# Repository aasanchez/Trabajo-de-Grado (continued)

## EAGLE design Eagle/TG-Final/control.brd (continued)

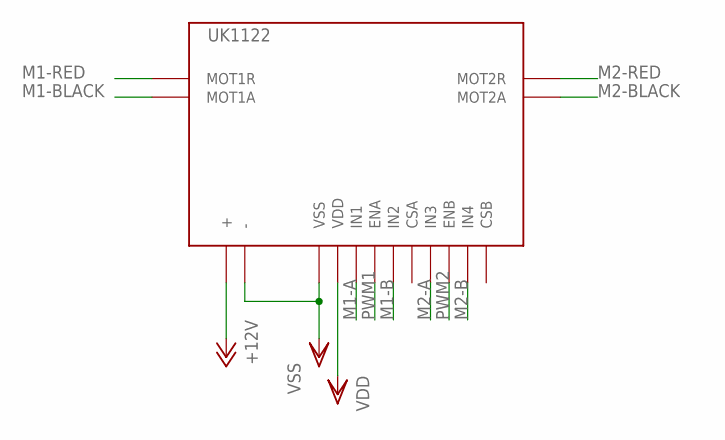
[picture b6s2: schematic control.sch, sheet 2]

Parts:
UK1122: UK1122

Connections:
+12V: UK1122.+; also elsewhere on the board
M1-A: UK1122.IN1; also elsewhere on the board
M1-B: UK1122.EN2 (IN2); also elsewhere on the board
M1-BLACK: UK1122.MOT1A; also elsewhere on the board
M1-RED: UK1122.MOT1R; also elsewhere on the board
M2-A: UK1122.IN3; also elsewhere on the board
M2-B: UK1122.IN4; also elsewhere on the board
M2-BLACK: UK1122.MOT2A; also elsewhere on the board
M2-RED: UK1122.MOT2R; also elsewhere on the board
PWM1: UK1122.ENA; also elsewhere on the board
PWM2: UK1122.ENB; also elsewhere on the board
VDD: UK1122.+5 (VDD); also elsewhere on the board
VSS: UK1122.-, UK1122.GND (VSS); also elsewhere on the board

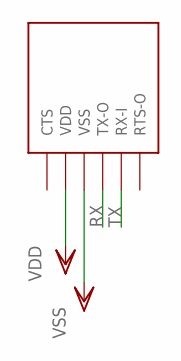
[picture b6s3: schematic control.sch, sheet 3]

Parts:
U$3: BLUESMIRF

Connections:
RX: U$3.TX-O; also elsewhere on the board
TX: U$3.RX-I; also elsewhere on the board
VDD: U$3.VDD; also elsewhere on the board
VSS: U$3.VSS; also elsewhere on the board

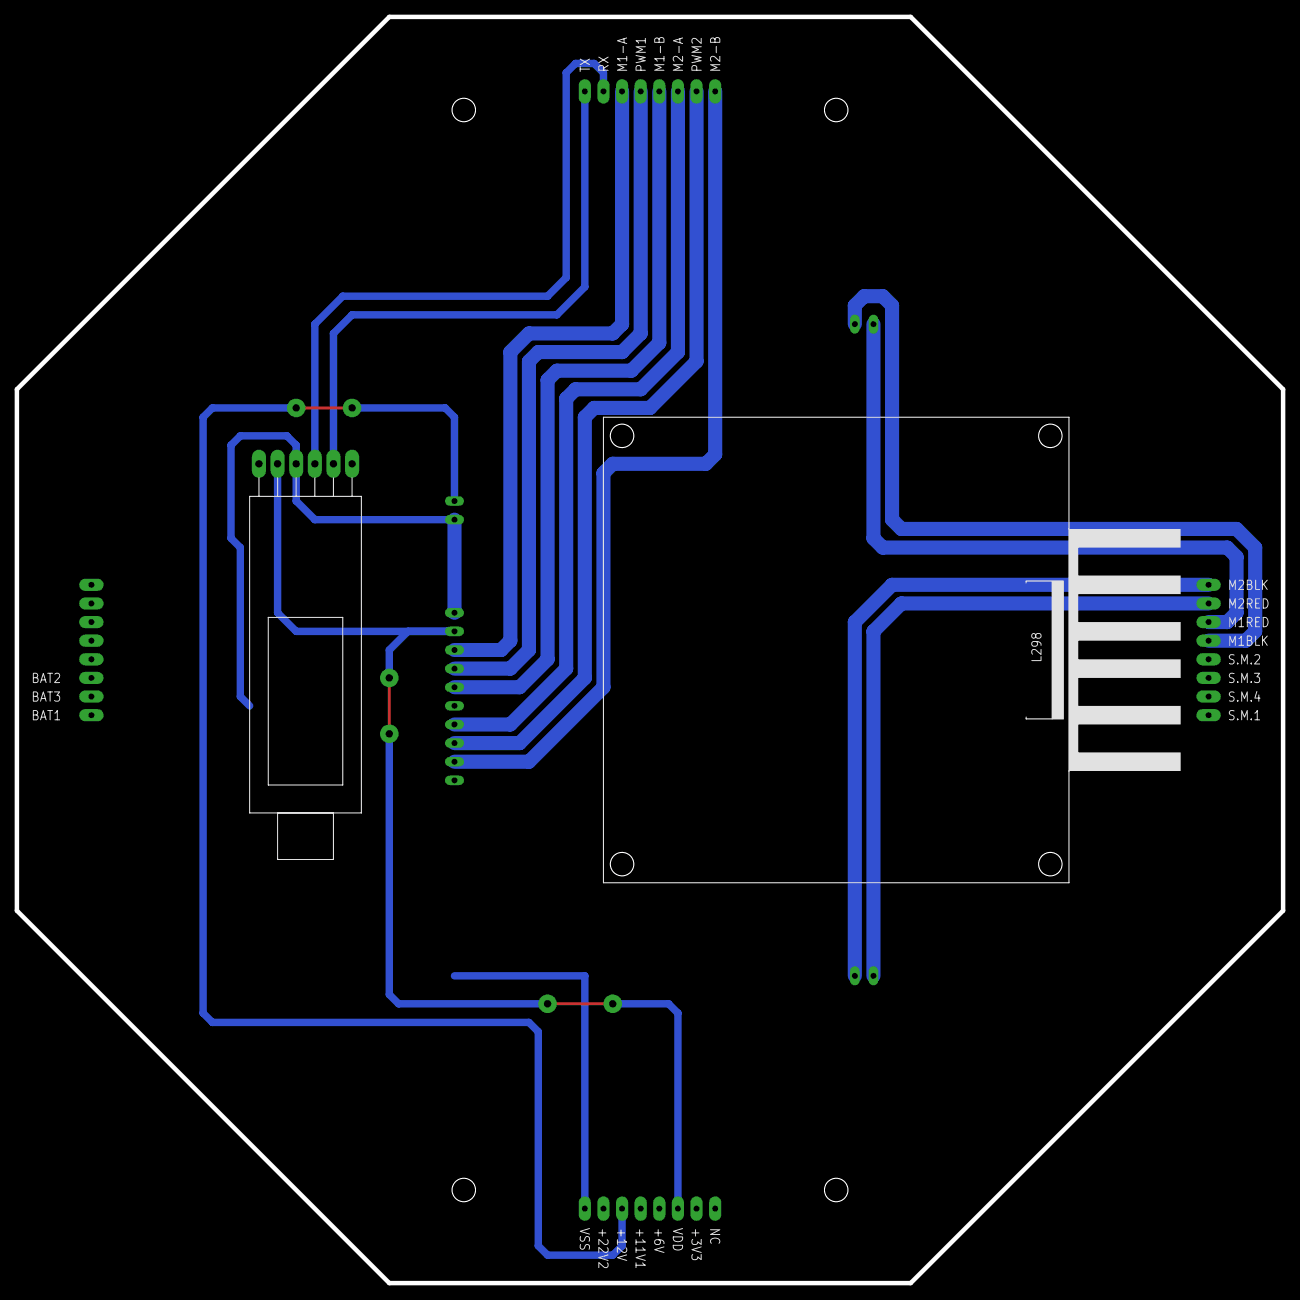
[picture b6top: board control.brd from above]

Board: 2 copper layers, 172.7 x 172.7 mm, 3 parts (0 on the bottom side), 15 nets.

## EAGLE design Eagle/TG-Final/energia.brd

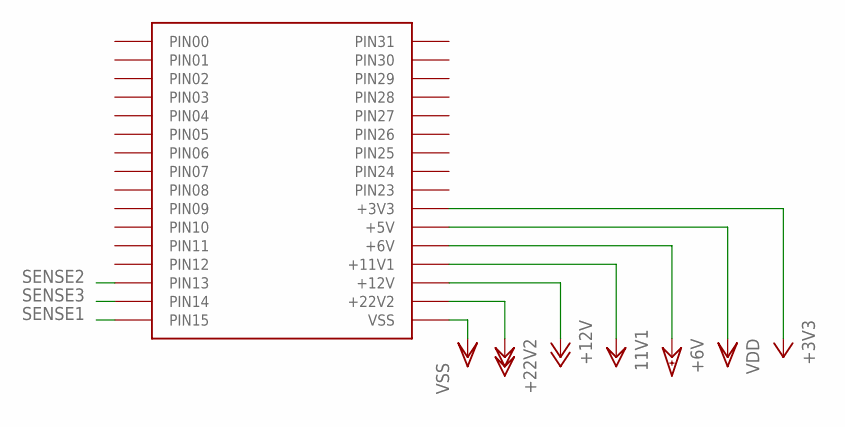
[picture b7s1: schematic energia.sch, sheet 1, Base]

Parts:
U$1: BASE

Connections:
+3V3: U$1.PIN22 (+3V3); also elsewhere on the board
+6V: U$1.PIN20 (+6V); also elsewhere on the board
+11V1: U$1.PIN19 (+11V1); also elsewhere on the board
+12V: U$1.PIN18 (+12V); also elsewhere on the board
+22V: U$1.PIN17 (+22V2); also elsewhere on the board
SENSE1: U$1.PIN15; also elsewhere on the board
SENSE2: U$1.PIN13; also elsewhere on the board
SENSE3: U$1.PIN14; also elsewhere on the board
VDD: U$1.PIN21 (+5V); also elsewhere on the board
VSS: U$1.PIN16 (VSS); also elsewhere on the board

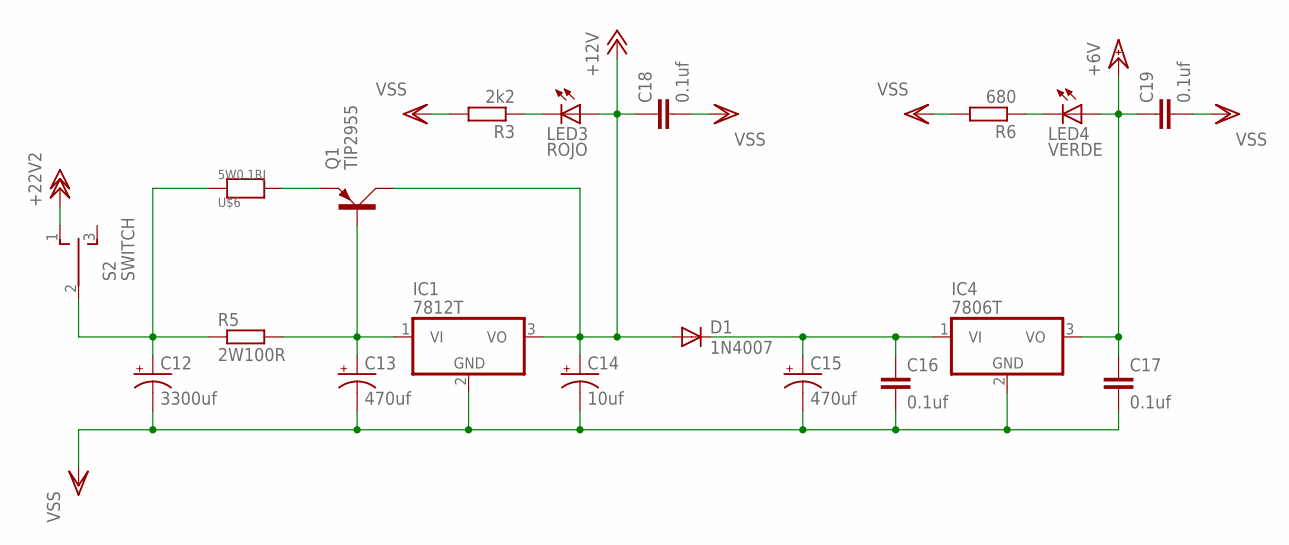
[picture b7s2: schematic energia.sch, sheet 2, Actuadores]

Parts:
C12: 3300uf; E7,5-18
C13, C15: 470uf; E3,5-8
C14: 10uf; E2,5-5
C16, C17, C18, C19: 0.1uf; C050-024X044
D1: 1N4007; DO41-10
IC1: 7812T; TO220H
IC4: 7806T; TO220H
LED3: ROJO; LED3MM
LED4: VERDE; LED3MM
Q1: TIP2955; TOP3AV
R3: 2k2; 0204/5
R5: 2W100R; 0411/12
R6: 680; 0204/5
S2: SWITCH; TL3XYO
U$6: 5W0.1RJ; RES-22X10

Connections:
+6V: C17.1, C19.1, IC4.3 (VO), LED4.A; also elsewhere on the board
+12V: C14.+, C18.1, D1.A, IC1.3 (VO), LED3.A, Q1.C; also elsewhere on the board
+22V: S2.1 (O); also elsewhere on the board
unnamed: LED3.K (C), R3.1
unnamed: C12.+, R5.1, S2.2, U$6.P$1
unnamed: Q1.E, U$6.P$2
unnamed: C13.+, IC1.1 (VI), Q1.B, R5.2
unnamed: LED4.K (C), R6.1
unnamed: C15.+, C16.1, D1.C, IC4.1 (VI)
VSS: C12.-, C13.-, C14.-, C15.-, C16.2, C17.2, C18.2, C19.2, IC1.2 (GND), IC4.2 (GND), R3.2, R6.2; also elsewhere on the board

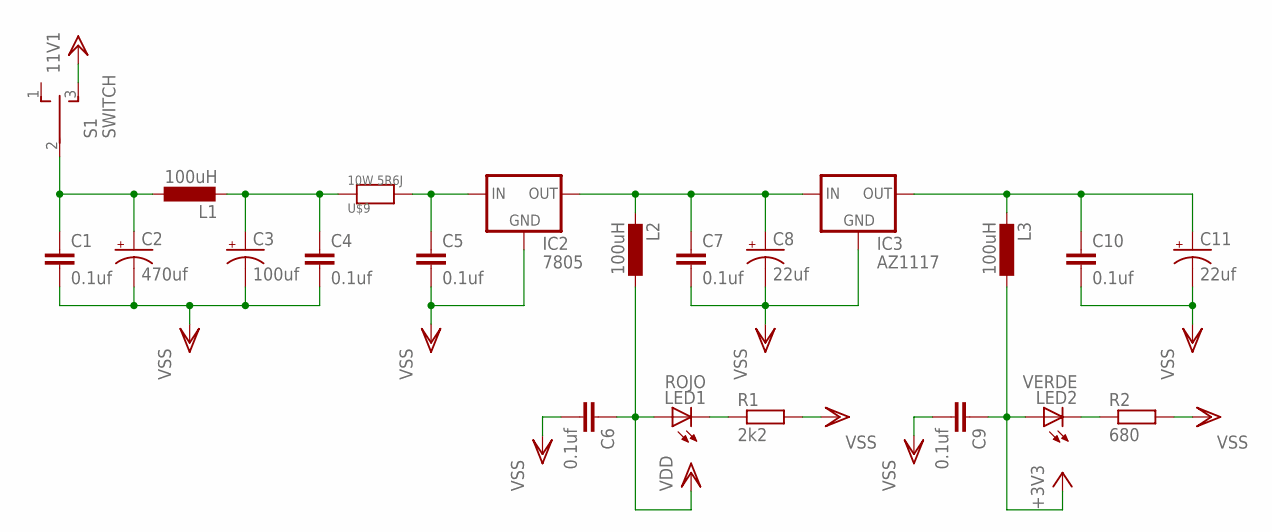
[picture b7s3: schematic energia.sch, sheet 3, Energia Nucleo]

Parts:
C1, C4, C5, C6, C7, C9, C10: 0.1uf; C050-024X044
C2: 470uf; E2,5-7
C3: 100uf; E2,5-7
C8, C11: 22uf; E2,5-7
IC2: 7805; TO-220-ALT
IC3: AZ1117; 78XXL
L1: 100uH; TFI0307
L2, L3: 100uH; 0207/7
LED1: ROJO; LED3MM
LED2: VERDE; LED3MM
R1: 2k2; 0204/5
R2: 680; 0204/5
S1: SWITCH; TL3XYO
U$9: 10W 5R6J; RES-49X10

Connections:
+3V3: C9.1, L3.1, LED2.A; also elsewhere on the board
+11V1: S1.3 (S); also elsewhere on the board
unnamed: C1.1, C2.+, L1.1, S1.2
unnamed: C5.1, IC2.IN, U$9.P$2
unnamed: C3.+, C4.1, L1.2, U$9.P$1
unnamed: C7.1, C8.+, IC2.OUT, IC3.OUT (IN), L2.2
unnamed: LED1.K (C), R1.1
unnamed: C10.1, C11.+, IC3.GND (OUT), L3.2
unnamed: LED2.K (C), R2.1
VDD: C6.1, L2.1, LED1.A; also elsewhere on the board
VSS: C1.2, C2.-, C3.-, C4.2, C5.2, C6.2, C7.2, C8.-, C9.2, C10.2, C11.-, IC2.GND, IC3.IN (GND), R1.2, R2.2; also elsewhere on the board

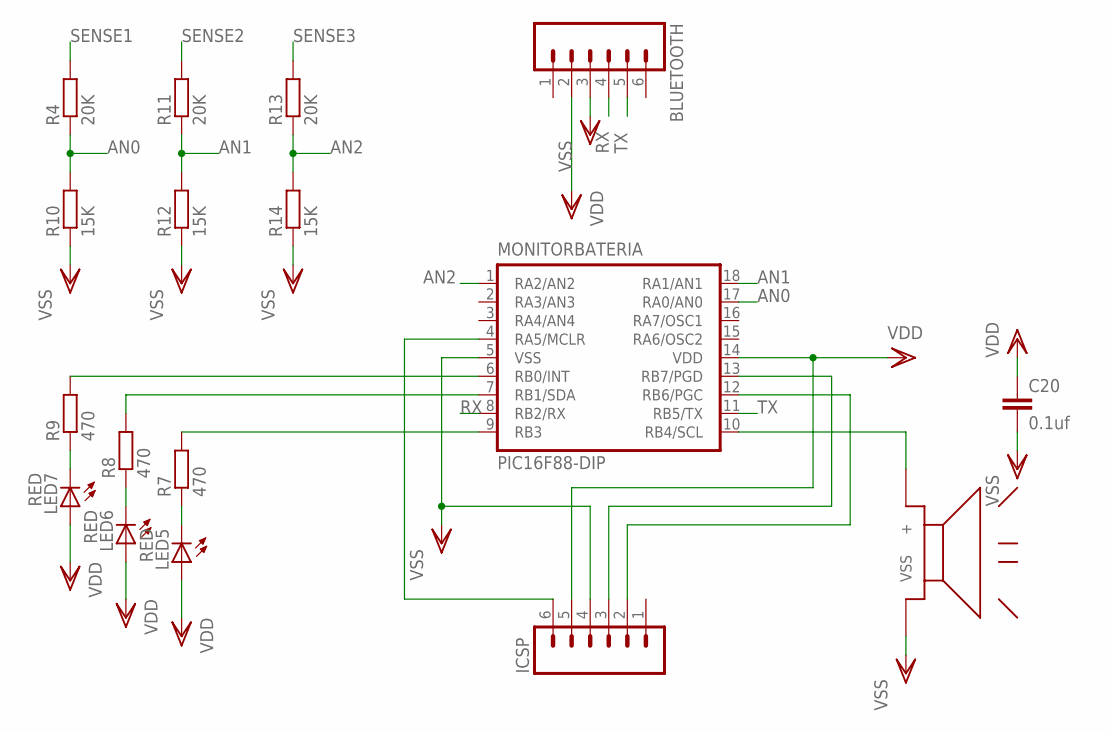
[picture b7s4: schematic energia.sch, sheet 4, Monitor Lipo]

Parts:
BLUETOOTH: 1X06_LONGPADS
C20: 0.1uf; C050-024X044
ICSP: 1X06_LONGPADS
LED5, LED6, LED7: RED; LED3MM
MONITORBATERIA: PIC16F88-DIP; DIL18
R4, R11, R13: 20K; 0204/5
R7, R8, R9: 470; 0204/5
R10, R12, R14: 15K; 0204/5
U$10: BUZZER

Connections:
AN0: MONITORBATERIA.17 (RA0/AN0), R4.1, R10.2
AN1: MONITORBATERIA.18 (RA1/AN1), R11.1, R12.2
AN2: MONITORBATERIA.1 (RA2/AN2), R13.1, R14.2
unnamed: ICSP.6, MONITORBATERIA.4 (RA5/MCLR)
unnamed: ICSP.3, MONITORBATERIA.13 (RB7/PGD)
unnamed: ICSP.2, MONITORBATERIA.12 (RB6/PGC)
unnamed: LED5.K (C), R7.1
unnamed: LED7.K (C), R9.1
unnamed: LED6.K (C), R8.1
unnamed: MONITORBATERIA.6 (RB0/INT), R9.2
unnamed: MONITORBATERIA.7 (RB1/SDA), R8.2
unnamed: MONITORBATERIA.9 (RB3), R7.2
unnamed: MONITORBATERIA.10 (RB4/SCL), U$10.+
RX: BLUETOOTH.4, MONITORBATERIA.8 (RB2/RX)
SENSE1: R4.2; also elsewhere on the board
SENSE2: R11.2; also elsewhere on the board
SENSE3: R13.2; also elsewhere on the board
TX: BLUETOOTH.5, MONITORBATERIA.11 (RB5/TX)
VDD: BLUETOOTH.2, C20.1, ICSP.5, LED5.A, LED6.A, LED7.A, MONITORBATERIA.14 (VDD); also elsewhere on the board
VSS: BLUETOOTH.3, C20.2, ICSP.4, MONITORBATERIA.5 (VSS), R10.1, R12.1, R14.1, U$10.- (VSS); also elsewhere on the board

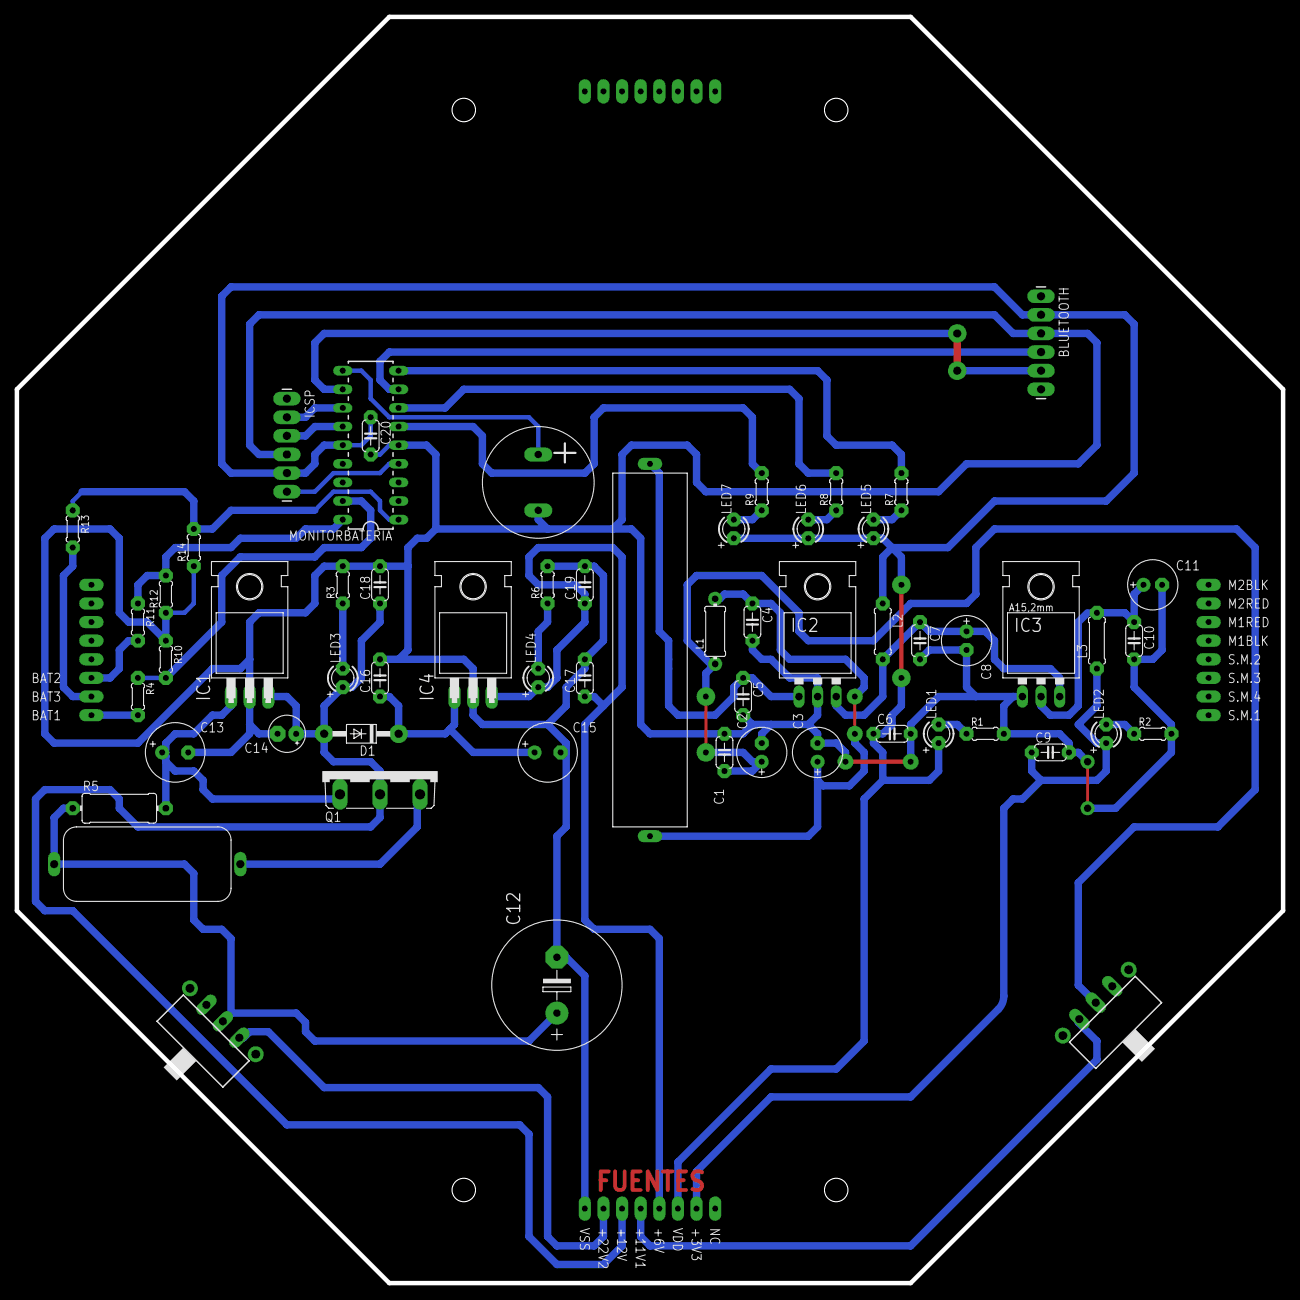
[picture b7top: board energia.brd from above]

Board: 2 copper layers, 172.7 x 172.7 mm, 59 parts (0 on the bottom side), 38 nets.

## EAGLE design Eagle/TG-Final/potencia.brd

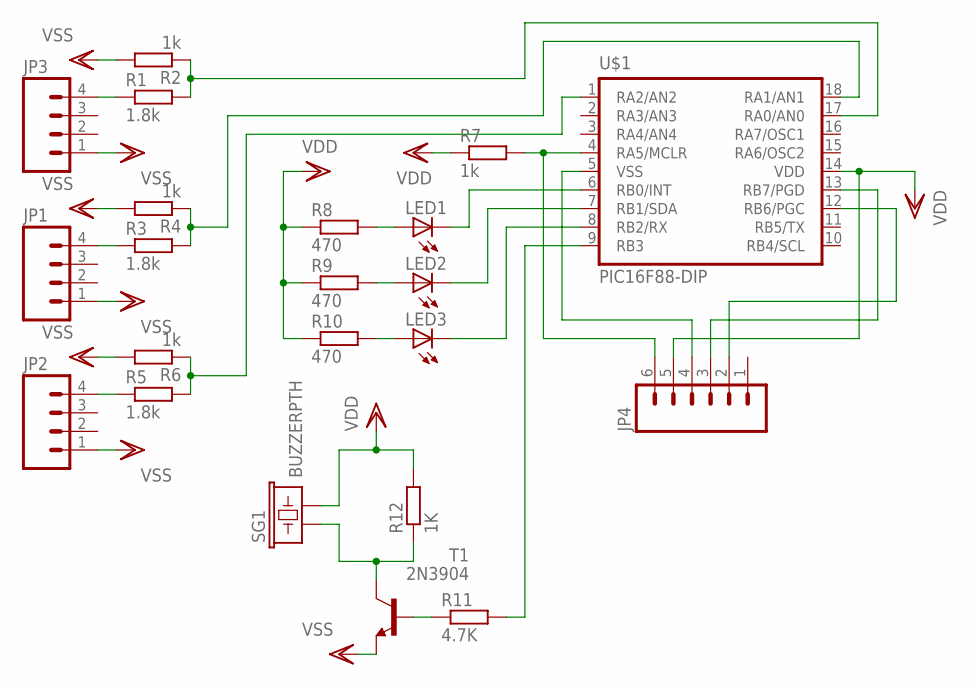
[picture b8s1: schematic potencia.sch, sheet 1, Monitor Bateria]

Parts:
JP1, JP2, JP3: M04LONGPADS; 1X04_LONGPADS
JP4: M06LONGPADS; 1X06_LONGPADS
LED1, LED2, LED3: LED3MM
R1, R3, R5: 1.8k; 0204/5
R2, R4, R6, R7: 1k; 0204/5
R8, R9, R10: 470; 0204/5
R11: 4.7K; 0204/5
R12: 1K; 0204/5
SG1: BUZZERPTH; BUZZER-12MM
T1: 2N3904; TO92
U$1: PIC16F88-DIP; DIL18

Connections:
unnamed: JP3.4, R1.1
unnamed: R1.2, R2.1, U$1.17 (RA0/AN0)
unnamed: JP1.4, R3.1
unnamed: R3.2, R4.1, U$1.18 (RA1/AN1)
unnamed: JP2.4, R5.1
unnamed: R5.2, R6.1, U$1.1 (RA2/AN2)
unnamed: JP4.4, U$1.5 (VSS)
unnamed: LED1.K (C), U$1.6 (RB0/INT)
unnamed: LED2.K (C), U$1.7 (RB1/SDA)
unnamed: LED3.K (C), U$1.8 (RB2/RX)
unnamed: LED1.A, R8.2
unnamed: JP4.3, U$1.13 (RB7/PGD)
unnamed: LED2.A, R9.2
unnamed: LED3.A, R10.2
unnamed: JP4.2, U$1.12 (RB6/PGC)
unnamed: JP4.6, R7.2, U$1.4 (RA5/MCLR)
unnamed: R11.2, U$1.9 (RB3)
unnamed: R11.1, T1.2 (B)
unnamed: R12.1, SG1.+ (1), T1.1 (C)
VDD: JP4.5, R7.1, R8.1, R9.1, R10.1, R12.2, SG1.- (2), U$1.14 (VDD)
VSS: JP1.1, JP2.1, JP3.1, R2.2, R4.2, R6.2, T1.3 (E); also elsewhere on the board

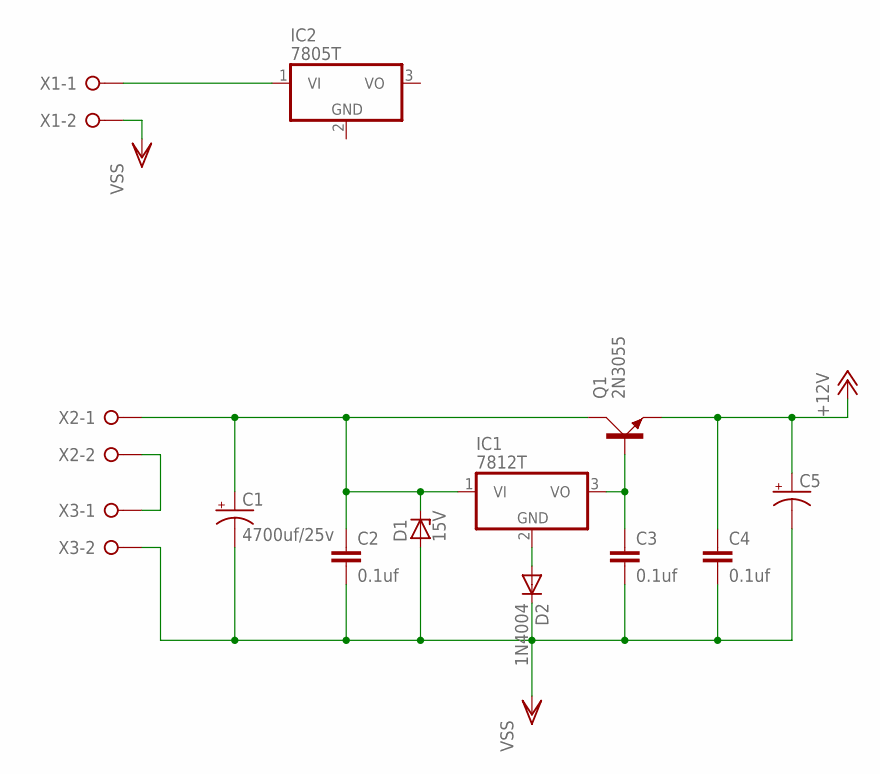
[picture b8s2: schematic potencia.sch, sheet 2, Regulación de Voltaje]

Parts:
C1: 4700uf/25v; EB30D
C2, C3, C4: 0.1uf; C050-024X044
C5: CPOL-USE2.5-6; E2,5-6
D1: 15V; F126Z10
D2: 1N4004; DO41-10
IC1: 7812T; TO220H
IC2: 7805T; TO220H
Q1: 2N3055; TO3A
X1, X2, X3: W237-2N

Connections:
+12V: C4.1, C5.+, Q1.E
unnamed: X2.2, X3.1
unnamed: C1.+, C2.1, D1.C, IC1.1 (VI), Q1.C, Q1.C1 (C), X2.1
unnamed: C3.1, IC1.3 (VO), Q1.B
unnamed: IC2.1 (VI), X1.1
unnamed: D2.A, IC1.2 (GND)
VSS: C1.-, C2.2, C3.2, C4.2, C5.-, D1.A, D2.C, X1.2, X3.2; also elsewhere on the board

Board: 2 copper layers, 35 parts (0 on the bottom side), 27 nets, no tracks yet.

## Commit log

2011-08-24 Primer commit
2011-10-05 codigo muñeco
2011-10-15 Actualizaciones General
2011-11-10 Lista de Compras
2012-01-18 Comienzo
2012-02-07 Actualizaciones Varias
2012-02-09 pySerial
2012-02-09 Limpiando
2012-02-13 Fixed
2012-02-13 Limpieza Profunda
2012-02-15 Codigo para graficas señales cortesia de Yeison Cardona
2012-02-16 Monitor Lipo
2012-02-16 Lectura 3 canales monitor de baterias
2012-02-16 Salidas en led alarma lipo
2012-02-16 Listo Codigo monitoreo Lipo 16f88
2012-02-16 inicio comunicacion CDC
2012-02-16 Graficas de IMU
2012-02-20 Inicio de Codigo Final
2012-02-20 Intento obtener datos del imu e una funcion
2012-02-22 Calibracion de Sensores
2012-02-22 Lectura y Optimizacion de Codigo
2012-02-23 Correccion para ADXL345 Eje Z, y graficas separadas
2012-02-24 Aceleración Angular
2012-03-01 Run Led
2012-03-02 Adquisición de sensores, limpieza de ruido y de calculo de zero, el cálculo del ángulo
2012-03-02 Filtro de Kalman
2012-03-02 iniciando de 298
2012-03-02 Fix Pin l298
2012-03-05 Comienzo de Control para Muñeco de Madera
2012-03-07 Diseño CAD y otros
2012-03-07 Schematic para Potencia
2012-03-08 Esquematicos de Alimentación
2012-03-08 Esquematicos para placa logica
2012-03-08 Fix Pins Motor 1, Avances en Esquematicos
2012-03-08 Limpieza, manual
2012-03-14 Placa de Actuadores y Otros
2012-03-14 Routing placa Actuadores
2012-03-14 Routing placa Actuadores. Listo??
2012-03-15 Mejoras en placa de Actuadores y otros
2012-03-16 Comienzo placa potencia
2012-03-19 Fuente 11.1v -> 5v y 3v3
2012-03-19 Monitor Baterias LiPO
2012-03-20 Correcciones varias
2012-03-23 Fuente de Potencia
2012-03-25 Trabajos en la Sub Estacion
2012-03-25 Reposicionando componentes en SubEstación
2012-03-26 Avanzando....
2012-03-26 Pruebas del Monitor de Baterias Lipo
2012-03-28 Peliando con un 16f88
2012-03-28 Sonido de alarma bajo Voltaje
2012-03-28 Barrido leds alarma
2012-03-29 Alias a algunas funciones monitor baterias lipo
2012-03-29 Lecturas Analogicas, problemas en resolución Aun
2012-03-29 Listo Monitor de 1 Bateria
2012-03-29 Completado Monitor de Bateria
2012-03-29 Placa Sub-Estación. Lista
2012-03-30 Placa de Control Motores y Comunicación
2012-03-31 Listo Placas
2012-04-08 Agregar datasheet 168
2012-04-08 Limpieza de Archivos Viejos
2012-04-09 Diagrama de Procesos
2012-04-09 Diagrama de Procesos General
2012-04-09 Avanzando con los Graficos
2012-04-09 Informe Pre-defensa; Esquematicos listos
2012-04-09 Fix: Aceleración Angular
2012-04-10 Pruebas Movimiento 1 Motor
2012-04-11 Fix: Polaridad Motores
2012-04-11 Fix: Pines PWM
2012-04-11 Divide y Podras (Quizas) Vencer
2012-04-12 Pruebas lectura IMU3000 Combo
2012-04-12 Estabilidad Estatica... Funcionando
2012-04-13 Limpieza de cosas que ya no van
2012-04-15 Nuevo diseño
2012-04-16 Haciendo el Informe
2012-04-17 Avanzando en los libros
2012-04-17 La redaccion no es lo mio
2012-04-18 Siento que la vida se me va en cada tecla... la redaccion es horrible
2012-04-23 Muchos Cambios a 2 dias de la denfesa
